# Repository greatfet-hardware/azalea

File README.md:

# Azalea

Hardware licensed under the BSD 3 clause license
Documentation licensed under the BSD 3 clause license

This repository contains the KiCad design for Azalea, also known as GreatFET One.  The design requires:

https://github.com/greatscottgadgets/gsg-kicad-lib

If you are using git, the preferred way to install gsg-kicad-lib is to use the submodule:

```
git submodule init && git submodule update
```

## Overview

Also known as GreatFET One, Azalea is the main board of the GreatFET project.

Azalea is a peripheral interface tool.  By adding expansion boards called "neighbors", you can turn Azalea into a USB peripheral that does almost anything.

Features:
* LPC4330 microcontroller (U1)
* Hi-Speed USB port (USB0) for connection to a host computer
* Expansion interface (J1 and J2) of 80 pins (2 female headers with 2 rows of 20 pins)
* Bonus row of 20 male pins (J7)
* 4 indicator LEDs
* 2 buttons, primarily for development (DFU and RESET, just like HackRF One)
* Full Speed USB port (USB1) for connection to a target (for [Facedancer](https://github.com/usb-tools/Facedancer))
* Power switching for use of USB1 as either host or device
* 3.3 V regulator that can supply some power to neighbors
* 2 MB flash memory
* Unpopulated Cortex Debug Header (J5) for JTAG or SWD

Except where noted below, all pins on expansion ports use 3.3 V I/O voltage.

## J1 (NEIGHBOR1) Pinout

Pin|Symbol|Special Function|Notes    |U1 Pin|GPIO |U0 |U1 |U2  |EMC        |SGPIO|ENET      |CAN1|SSP0|SSP1|I2S0           |I2S1  |USB0     |USB1     |SD   |MISC   |PWM  |TIMER  |SCT     
---|------|----------------|---------|------|-----|---|---|----|-----------|-----|----------|----|----|----|---------------|------|---------|---------|-----|-------|-----|-------|--------
1  |GND   |                |         |      |     |   |   |    |           |     |          |    |    |    |               |      |         |         |     |       |     |       |        
2  |VCC   |                |3.3 V    |      |     |   |   |    |           |     |          |    |    |    |               |      |         |         |     |       |     |       |        
3  |P4_9  |                |         |33    |5[13]|   |   |    |           |14   |          |RD  |    |    |               |      |         |         |     |       |     |       |CTIN_6  
4  |P0_0  |                |         |32    |0[0] |   |   |    |           |0    |RXD1      |    |    |CIPO|TX_WS          |TX_WS |         |         |     |       |     |       |        
5  |P4_10 |                |         |35    |5[14]|   |   |    |           |15   |          |    |    |    |               |      |         |         |     |       |     |       |CTIN_2  
6  |P0_1  |                |         |34    |0[1] |   |   |    |           |1    |TX_EN     |    |    |COPI|               |TX_SDA|         |         |     |       |     |       |        
7  |P1_0  |                |         |38    |0[4] |   |   |    |A5         |7    |          |    |CS  |    |               |      |         |         |     |       |     |       |CTIN_3  
8  |P5_0  |                |         |37    |2[9] |   |DSR|    |D12        |     |          |    |    |    |               |      |         |         |     |       |MCOB2|T1_CAP0|        
9  |P5_1  |                |         |39    |2[10]|   |DTR|    |D13        |     |          |    |    |    |               |      |         |         |     |       |MCI2 |T1_CAP1|        
10 |P1_1  |boot mode       |pull-up  |42    |0[8] |   |   |    |A6         |8    |          |    |CIPO|    |               |      |         |         |     |       |     |       |CTOUT_7 
11 |CLK0  |                |         |45    |     |   |   |    |CLK0, CLK01|     |REF_CLK   |    |    |SCK |               |      |         |         |CLK  |CLKOUT |     |       |        
12 |P1_2  |boot mode       |pull-down|43    |0[9] |   |   |    |A7         |9    |          |    |COPI|    |               |      |         |         |     |       |     |       |CTOUT_6 
13 |P1_5  |                |         |48    |1[8] |   |   |    |CS0#       |15   |          |    |    |CS  |               |      |PWR_FAULT|         |POW  |       |     |       |CTOUT_10
14 |P5_2  |                |         |46    |2[11]|   |RTS|    |D14        |     |          |    |    |    |               |      |         |         |     |       |MCI1 |T1_CAP2|        
15 |P1_7  |                |         |50    |1[0] |   |DSR|    |D0         |     |          |    |    |    |               |      |PPWR     |         |     |       |     |       |CTIN_1  
16 |P1_6  |                |         |49    |1[9] |   |   |    |WE#        |14   |          |    |    |    |               |      |         |         |CMD  |       |     |       |CTIN_5  
17 |P1_9  |                |         |52    |1[2] |   |RTS|    |D2         |     |          |    |    |    |               |      |         |         |DAT0 |       |     |       |CTOUT_11
18 |P1_8  |                |         |51    |1[1] |   |DTR|    |D1         |     |          |    |    |    |               |      |         |         |VOLT0|       |     |       |CTOUT_12
19 |P5_3  |                |         |54    |2[12]|   |RI |    |D15        |     |          |    |    |    |               |      |         |         |     |       |MCI0 |T1_CAP3|        
20 |P1_10 |                |         |53    |1[3] |   |RI |    |D3         |     |          |    |    |    |               |      |         |         |DAT1 |       |     |       |CTOUT_14
21 |P1_12 |                |         |56    |1[5] |   |DCD|    |D5         |8    |          |    |    |    |               |      |         |         |DAT3 |       |     |T0_CAP1|        
22 |P1_11 |                |         |55    |1[4] |   |CTS|    |D4         |     |          |    |    |    |               |      |         |         |DAT2 |       |     |       |CTOUT_15
23 |P5_5  |                |         |58    |2[14]|   |DCD|    |D9         |     |          |    |    |    |               |      |         |         |     |       |MCOA1|T1_MAT1|        
24 |P5_4  |                |         |57    |2[13]|   |CTS|    |D8         |     |          |    |    |    |               |      |         |         |     |       |MCOB0|T1_MAT0|        
25 |P1_14 |                |         |61    |1[7] |   |RXD|    |D7         |10   |          |    |    |    |               |      |         |         |     |       |     |T0_MAT2|        
26 |P1_13 |                |         |60    |1[6] |   |TXD|    |D6         |9    |          |    |    |    |               |      |         |         |CD   |       |     |T0_CAP0|        
27 |P5_6  |                |         |63    |2[15]|   |TXD|    |D10        |     |          |    |    |    |               |      |         |         |     |       |MCOB1|T1_MAT2|        
28 |P1_15 |                |         |62    |0[2] |   |   |TXD |           |2    |RXD0      |    |    |    |               |      |         |         |     |       |     |T0_MAT1|        
29 |P5_7  |                |         |65    |2[7] |   |RXD|    |D11        |     |          |    |    |    |               |      |         |         |     |       |     |T1_MAT3|        
30 |P1_16 |                |         |64    |0[3] |   |   |RXD |           |3    |CRS, RX_DV|    |    |    |               |      |         |         |     |       |MCOA2|T0_MAT0|        
31 |P1_18 |                |         |67    |0[13]|   |   |DIR |           |12   |TXD0      |RD  |    |    |               |      |         |         |     |       |     |T0_MAT3|        
32 |P1_17 |                |         |66    |0[12]|   |   |UCLK|           |11   |MDIO      |TD  |    |    |               |      |         |         |     |       |     |T0_CAP3|        
33 |P9_5  |                |         |69    |5[18]|TXD|   |    |           |3    |          |    |    |    |               |      |         |PPWR     |     |       |MCOA1|       |        
34 |P9_6  |                |         |72    |4[11]|RXD|   |    |           |8    |          |    |    |    |               |      |         |PWR_FAULT|     |       |MCOB1|       |        
35 |P2_0  |                |         |75    |5[0] |TXD|   |    |A13        |4    |MDC       |    |    |    |               |      |PPWR     |         |     |ISP_TXD|     |T3_CAP0|        
36 |P6_0  |                |         |73    |     |   |   |    |           |     |          |    |    |    |RX_MCLK, RX_SCK|      |         |         |     |       |     |       |        
37 |P1_20 |                |         |70    |0[15]|   |   |    |           |13   |TXD1      |    |    |CS  |               |      |         |         |     |       |     |T0_CAP2|        
38 |P1_19 |                |         |68    |     |   |   |    |           |     |REF_CLK   |    |    |SCK |RX_MCLK        |TX_SCK|         |         |     |CLKOUT |     |       |        
39 |P1_4  |                |         |47    |0[11]|   |   |    |BLS0#      |11   |          |    |    |COPI|               |      |IND0     |         |VOLT1|       |     |       |CTOUT_9 
40 |P1_3  |                |         |44    |0[10]|   |   |    |OE#        |10   |          |    |    |CIPO|               |      |IND1     |         |     |       |     |       |CTOUT_8 

## J2 (NEIGHBOR2) Pinout

Pin|Symbol  |Special Function|Notes            |U1 Pin|GPIO |U0  |U1 |U2 |U3  |EMC        |SGPIO|RMII|CAN0|CAN1|SPI |SSP0      |SSP1|SPIFI|I2S0                            |I2S1  |I2C0|I2C1|USB0     |USB1|SD |ADC     |MISC              |PWM  |TIMER  |SCT     
---|--------|----------------|-----------------|------|-----|----|---|---|----|-----------|-----|----|----|----|----|----------|----|-----|--------------------------------|------|----|----|---------|----|---|--------|------------------|-----|-------|--------
1  |GND     |                |                 |      |     |    |   |   |    |           |     |    |    |    |    |          |    |     |                                |      |    |    |         |    |   |        |                  |     |       |        
2  |5V      |                |                 |      |     |    |   |   |    |           |     |    |    |    |    |          |    |     |                                |      |    |    |         |    |   |        |                  |     |       |        
3  |P4_8    |                |                 |15    |5[12]|    |   |   |    |           |13   |    |    |TD  |    |          |    |     |                                |      |    |    |         |    |   |        |                  |     |       |CTIN_5  
4  |P4_0    |                |                 |1     |2[0] |    |   |   |UCLK|           |     |    |    |    |    |          |    |     |                                |      |    |    |         |    |   |        |NMI               |MCOA0|       |        
5  |ADC0_0  |                |                 |6     |     |    |   |   |    |           |     |    |    |    |    |          |    |     |                                |      |    |    |         |    |   |0_0, 1_0|DAC               |     |       |        
6  |P4_5    |                |                 |10    |2[5] |    |   |   |    |           |11   |    |    |    |    |          |    |     |                                |      |    |    |         |    |   |        |                  |     |       |CTOUT_5 
7  |P4_4    |                |                 |9     |2[4] |    |   |   |DIR |           |10   |    |    |    |    |          |    |     |                                |      |    |    |         |    |   |        |DAC               |     |       |CTOUT_2 
8  |P4_2    |                |                 |8     |2[2] |    |   |   |RXD |           |8    |    |    |    |    |          |    |     |                                |      |    |    |         |    |   |        |                  |     |       |CTOUT_0 
9  |P4_3    |                |                 |7     |2[3] |    |   |   |BAUD|           |9    |    |    |    |    |          |    |     |                                |      |    |    |         |    |   |0_0     |                  |     |       |CTOUT_3 
10 |P4_6    |                |                 |11    |2[6] |    |   |   |    |           |12   |    |    |    |    |          |    |     |                                |      |    |    |         |    |   |        |                  |     |       |CTOUT_4 
11 |P4_7    |                |                 |14    |     |    |   |   |    |           |     |    |    |    |    |          |    |     |TX_SCK                          |TX_SCK|    |    |         |    |   |        |GP_CLKIN          |     |       |        
12 |CLK2    |                |                 |99    |     |    |   |   |    |CLK3, CLK23|     |    |    |    |    |          |    |     |TX_MCLK                         |RX_SCK|    |    |         |    |CLK|        |CLKOUT            |     |       |        
13 |P2_8    |DFU, boot mode  |pull-down, button|98    |5[7] |    |   |   |DIR |A8         |15   |    |    |    |    |          |    |     |                                |      |    |    |         |    |   |        |                  |     |       |CTOUT_0 
14 |P2_7    |ISP, boot mode  |pull-up          |96    |0[7] |    |   |   |UCLK|A9         |     |    |    |    |    |          |    |     |                                |      |    |    |         |    |   |        |                  |     |T3_MAT3|CTOUT_1 
15 |P2_6    |                |                 |95    |5[6] |DIR |   |   |    |A10        |7    |    |    |    |    |          |    |     |                                |      |    |    |IND0     |    |   |        |                  |     |T3_CAP3|CTIN_7  
16 |P7_7    |                |                 |140   |3[15]|    |   |   |    |           |7    |MDC |    |    |    |          |    |     |                                |      |    |    |         |    |   |1_6     |TRACEDATA[3]      |     |       |CTOUT_8 
17 |WAKEUP0 |                |pull-up          |130   |     |    |   |   |    |           |     |    |    |    |    |          |    |     |                                |      |    |    |         |    |   |        |WAKEUP0           |     |       |        
18 |P2_5    |                |                 |91    |5[5] |    |   |   |    |           |14   |    |    |    |    |          |    |     |                                |      |    |    |IND0     |VBUS|   |TRIG1   |                  |     |T3_MAT2|CTIN_2  
19 |P2_4    |                |                 |88    |5[4] |    |   |   |RXD |           |13   |    |    |    |    |          |    |     |                                |      |    |SCL |PWR_FAULT|    |   |        |                  |     |T3_MAT1|CTIN_0  
20 |P2_3    |                |                 |87    |5[3] |    |   |   |TXD |           |12   |    |    |    |    |          |    |     |                                |      |    |SDA |PPWR     |    |   |        |                  |     |T3_MAT0|CTIN_1  
21 |PF_4    |                |                 |120   |     |    |   |   |    |           |     |    |    |    |    |          |SCK |     |TX_MCLK, RX_SCK                 |      |    |    |         |    |   |        |GP_CLKIN, TRACECLK|     |       |        
22 |P3_2    |                |                 |116   |5[9] |    |   |   |    |           |     |    |TD  |    |    |          |    |     |TX_SDA, RX_SDA                  |      |    |    |         |IND0|   |        |                  |     |       |        
23 |P7_2    |                |                 |115   |3[10]|    |   |RXD|    |           |6    |    |    |    |    |          |    |     |TX_SDA                          |      |    |    |         |    |   |        |                  |     |       |CTIN_4  
24 |P3_1    |                |                 |114   |5[8] |    |   |   |    |           |     |    |RD  |    |    |          |    |     |TX_WS, RX_WS                    |      |    |    |         |IND1|   |        |                  |     |       |        
25 |P7_1    |                |                 |113   |3[9] |    |   |TXD|    |           |5    |    |    |    |    |          |    |     |TX_WS                           |      |    |    |         |    |   |        |                  |     |       |CTOUT_15
26 |P3_0    |                |                 |112   |     |    |   |   |    |           |     |    |    |    |    |SCK       |    |     |RX_SCK, RX_MCLK, TX_SCK, TX_MCLK|      |    |    |         |    |   |        |                  |     |       |        
27 |P7_0    |                |                 |110   |3[8] |    |   |   |    |           |4    |    |    |    |    |          |    |     |                                |      |    |    |         |    |   |        |                  |     |       |CTOUT_14
28 |P3_4    |                |                 |119   |1[14]|    |TXD|   |    |           |     |    |    |    |    |          |    |SIO3 |TX_WS                           |RX_SDA|    |    |         |    |   |        |                  |     |       |        
29 |P6_8    |                |                 |86    |5[16]|    |   |   |    |A14        |7    |    |    |    |    |          |    |     |                                |      |    |    |IND0     |    |   |        |                  |     |T2_MAT1|        
30 |P3_7    |                |                 |123   |5[10]|    |   |   |    |           |     |    |    |    |COPI|CIPO, COPI|    |COPI |                                |      |    |    |         |    |   |        |                  |     |       |        
31 |P6_7    |                |                 |85    |5[15]|    |   |   |    |A15        |6    |    |    |    |    |          |    |     |                                |      |    |    |IND1     |    |   |        |                  |     |T2_MAT0|        
32 |P3_3    |                |                 |118   |     |    |   |   |    |           |     |    |    |    |SCK |SCK       |    |SCK  |TX_MCLK                         |TX_SCK|    |    |         |    |   |        |CGU_OUT1          |     |       |        
33 |P2_2    |                |                 |84    |5[2] |UCLK|   |   |    |A11        |6    |    |    |    |    |          |    |     |                                |      |    |    |IND1     |    |   |        |                  |     |T3_CAP2|CTIN_6  
34 |P6_6    |                |                 |83    |0[5] |    |   |   |    |BLS1#      |5    |    |    |    |    |          |    |     |                                |      |    |    |PWR_FAULT|    |   |        |                  |     |T2_CAP3|        
35 |P2_1    | neighbor WC    |                 |81    |5[1] |RXD |   |   |    |A12        |5    |    |    |    |    |          |    |     |                                |      |    |    |PWR_FAULT|    |   |        |ISP_RXD           |     |T3_CAP1|        
36 |P6_3    |                |                 |79    |3[2] |    |   |   |    |CS1#       |4    |    |    |    |    |          |    |     |                                |      |    |    |PPWR     |    |   |        |                  |     |T2_CAP2|        
37 |P3_5    |                |                 |121   |1[15]|    |RXD|   |    |           |     |    |    |    |    |          |    |SIO2 |TX_SDA                          |RX_WS |    |    |         |    |   |        |                  |     |       |        
38 |P3_6    |                |                 |122   |0[6] |    |   |   |    |           |     |    |    |    |CIPO|CS,   CIPO|    |CIPO |                                |      |    |    |         |    |   |        |                  |     |       |        
39 |I2C0_SDA|                |pull-up          |93    |     |    |   |   |    |           |     |    |    |    |    |          |    |     |                                |      |SDA |    |         |    |   |        |                  |     |       |        
40 |I2C0_SCL|                |pull-up          |92    |     |    |   |   |    |           |     |    |    |    |    |          |    |     |                                |      |SCL |    |         |    |   |        |                  |     |       |        

## J5 (JTAG) Pinout

Pin|Symbol    |Notes          |U1 Pin
---|----------|---------------|------
1  |VCC       |3.3 V          |      
2  |TMS/SWDIO |               |30    
3  |GND       |               |      
4  |TCK/SWDCLK|pull-up        |27    
5  |GND       |               |      
6  |TDO/SWO   |pull-up        |31    
7  |          |not connected  |      
8  |TDI       |               |26    
9  |GND       |               |      
10 |RESET#    |pull-up, button|128   

## J7 (BONUS_ROW) Pinout

Pin|Symbol       |Special Function|Notes          |U1 Pin|GPIO |U0  |U2  |U3  |EMC    |I2S0  |ADC     |PWM    |TIMER  |SCT    
---|-------------|----------------|---------------|------|-----|----|----|----|-------|------|--------|-------|-------|-------
1  |GND          |                |               |      |     |    |    |    |       |      |        |       |       |       
2  |P6_4         |                |               |80    |3[3] |TXD |    |    |CAS#   |      |        |       |       |CTIN_6 
3  |P6_5         |                |               |82    |3[4] |RXD |    |    |RAS#   |      |        |       |       |CTOUT_6
4  |ADC0_5/ADC1_5|                |               |144   |     |    |    |    |       |      |0_5, 1_5|       |       |       
5  |ADC0_2/ADC1_2|                |               |143   |     |    |    |    |       |      |0_2, 1_2|       |       |       
6  |P2_9         |boot mode       |pull-down      |102   |1[10]|    |    |BAUD|A0     |      |        |       |       |CTOUT_3
7  |P2_12        |                |               |106   |1[12]|    |UCLK|    |A3     |      |        |       |       |CTOUT_4
8  |P2_13        |                |               |108   |1[13]|    |DIR |    |A4     |      |        |       |       |CTIN_4 
9  |RTC_ALARM    |                |               |129   |     |    |    |    |       |      |        |       |       |       
10 |RTCX1        |                |               |      |     |    |    |    |       |      |        |       |       |       
11 |RESET#       |                |pull-up, button|128   |     |    |    |    |       |      |        |       |       |       
12 |VBAT         |                |               |127   |     |    |    |    |       |      |        |       |       |       
13 |P2_11        |                |               |105   |1[11]|    |RXD |    |A2     |      |        |       |       |CTOUT_5
14 |P2_10        |                |               |104   |0[14]|    |TXD |    |A1     |      |        |       |       |CTOUT_2
15 |P6_10        |                |               |100   |3[6] |    |    |    |DQMOUT1|      |        |MCABORT|       |       
16 |P6_9         |                |               |97    |3[5] |    |    |    |DYCS0# |      |        |       |T2_MAT2|       
17 |P6_2         |                |               |78    |3[1] |DIR |    |    |CKEOUT1|RX_SDA|        |       |T2_CAP1|       
18 |P6_1         |                |               |74    |3[0] |UCLK|    |    |DYCS1# |RX_WS |        |       |T2_CAP0|       
19 |GND          |                |               |      |     |    |    |    |       |      |        |       |       |       
20 |VCC          |                |3.3 V          |      |     |    |    |    |       |      |        |       |       |       

## Clear Acrylic Case

Hardware licensed under the BSD 3 clause license
Documentation licensed under the BSD 3 clause license

The vector graphic file provided in this repo was created with Inkscape.

The black lines are the edge cuts. The blue lines are cut outs. The red lines are optional and should be lightly etched if they are used.
The red lines are meant to be used to help count holes in the headers.

### The BOM 

* 4 x 4.5 mm OD Hex Standoffs (Female-Female) / M3-0.5 x 6 mm / Aluminum
* 4 x 4.5 mm OD Hex Standoffs (Female-Female) / M3-0.5 x 5 mm / Aluminum
* 4 x M3-0.5 x 12 mm / Phillips Pan Head Machine Screw
* 4 x M3-0.5 x 5 mm / Phillips Pan Head Machine Screw

Optional:
* 4 (per neighbor) x 4.5 mm OD Hex Standoffs (Male-Female) / M3-0.5 x 11 mm / Aluminum

These standoffs are to be used if a neighbor is stacked on your GreatFET One and you want your case to be stacked above that neighbor.

### Assembly Instructions 

Assembly instructions can be found [here.](https://www.greatscottgadgets.com/greatfet/acrylic-case/)

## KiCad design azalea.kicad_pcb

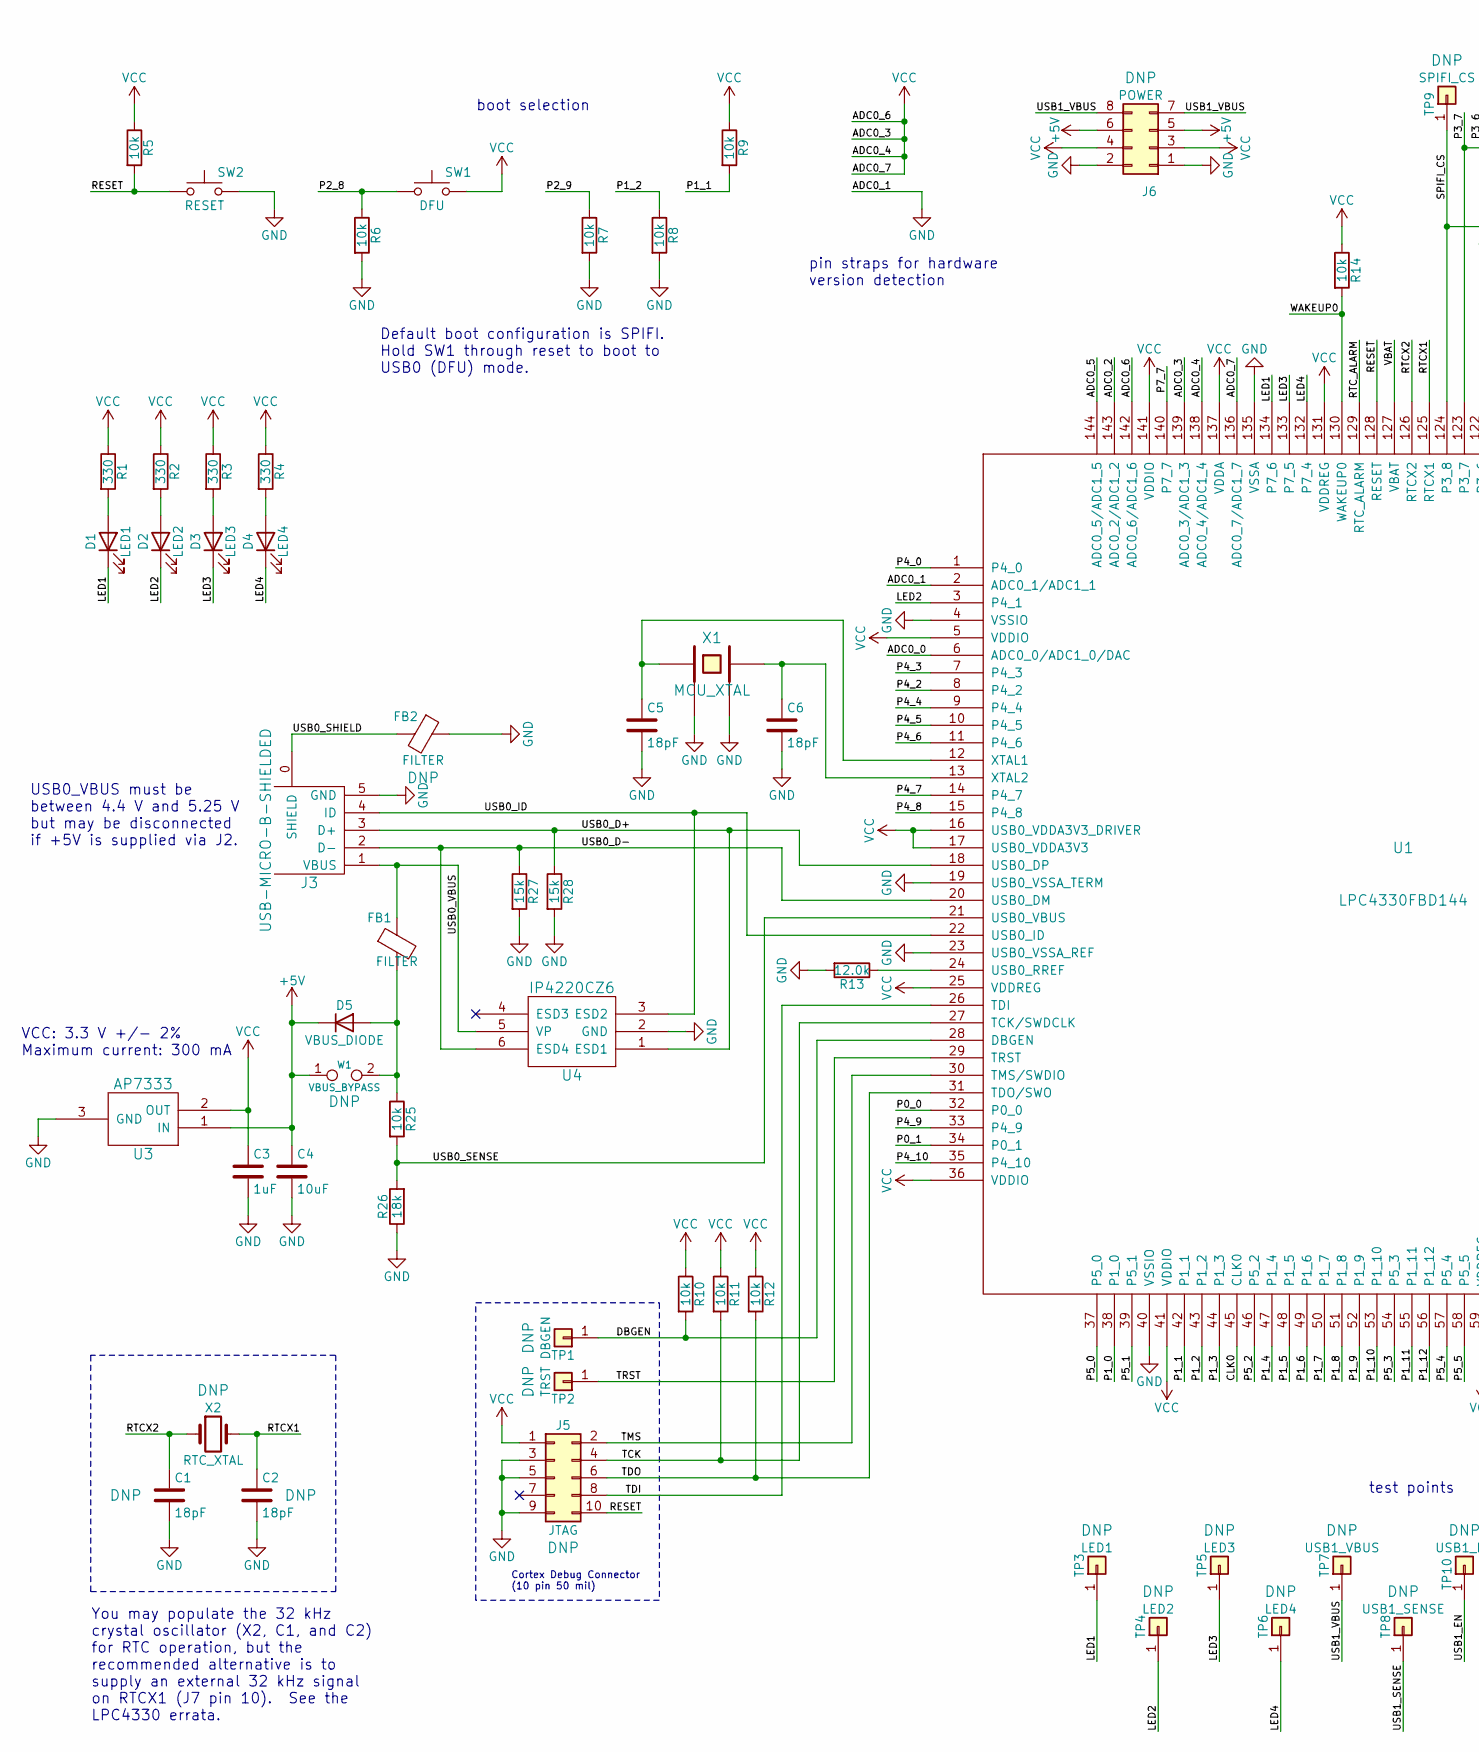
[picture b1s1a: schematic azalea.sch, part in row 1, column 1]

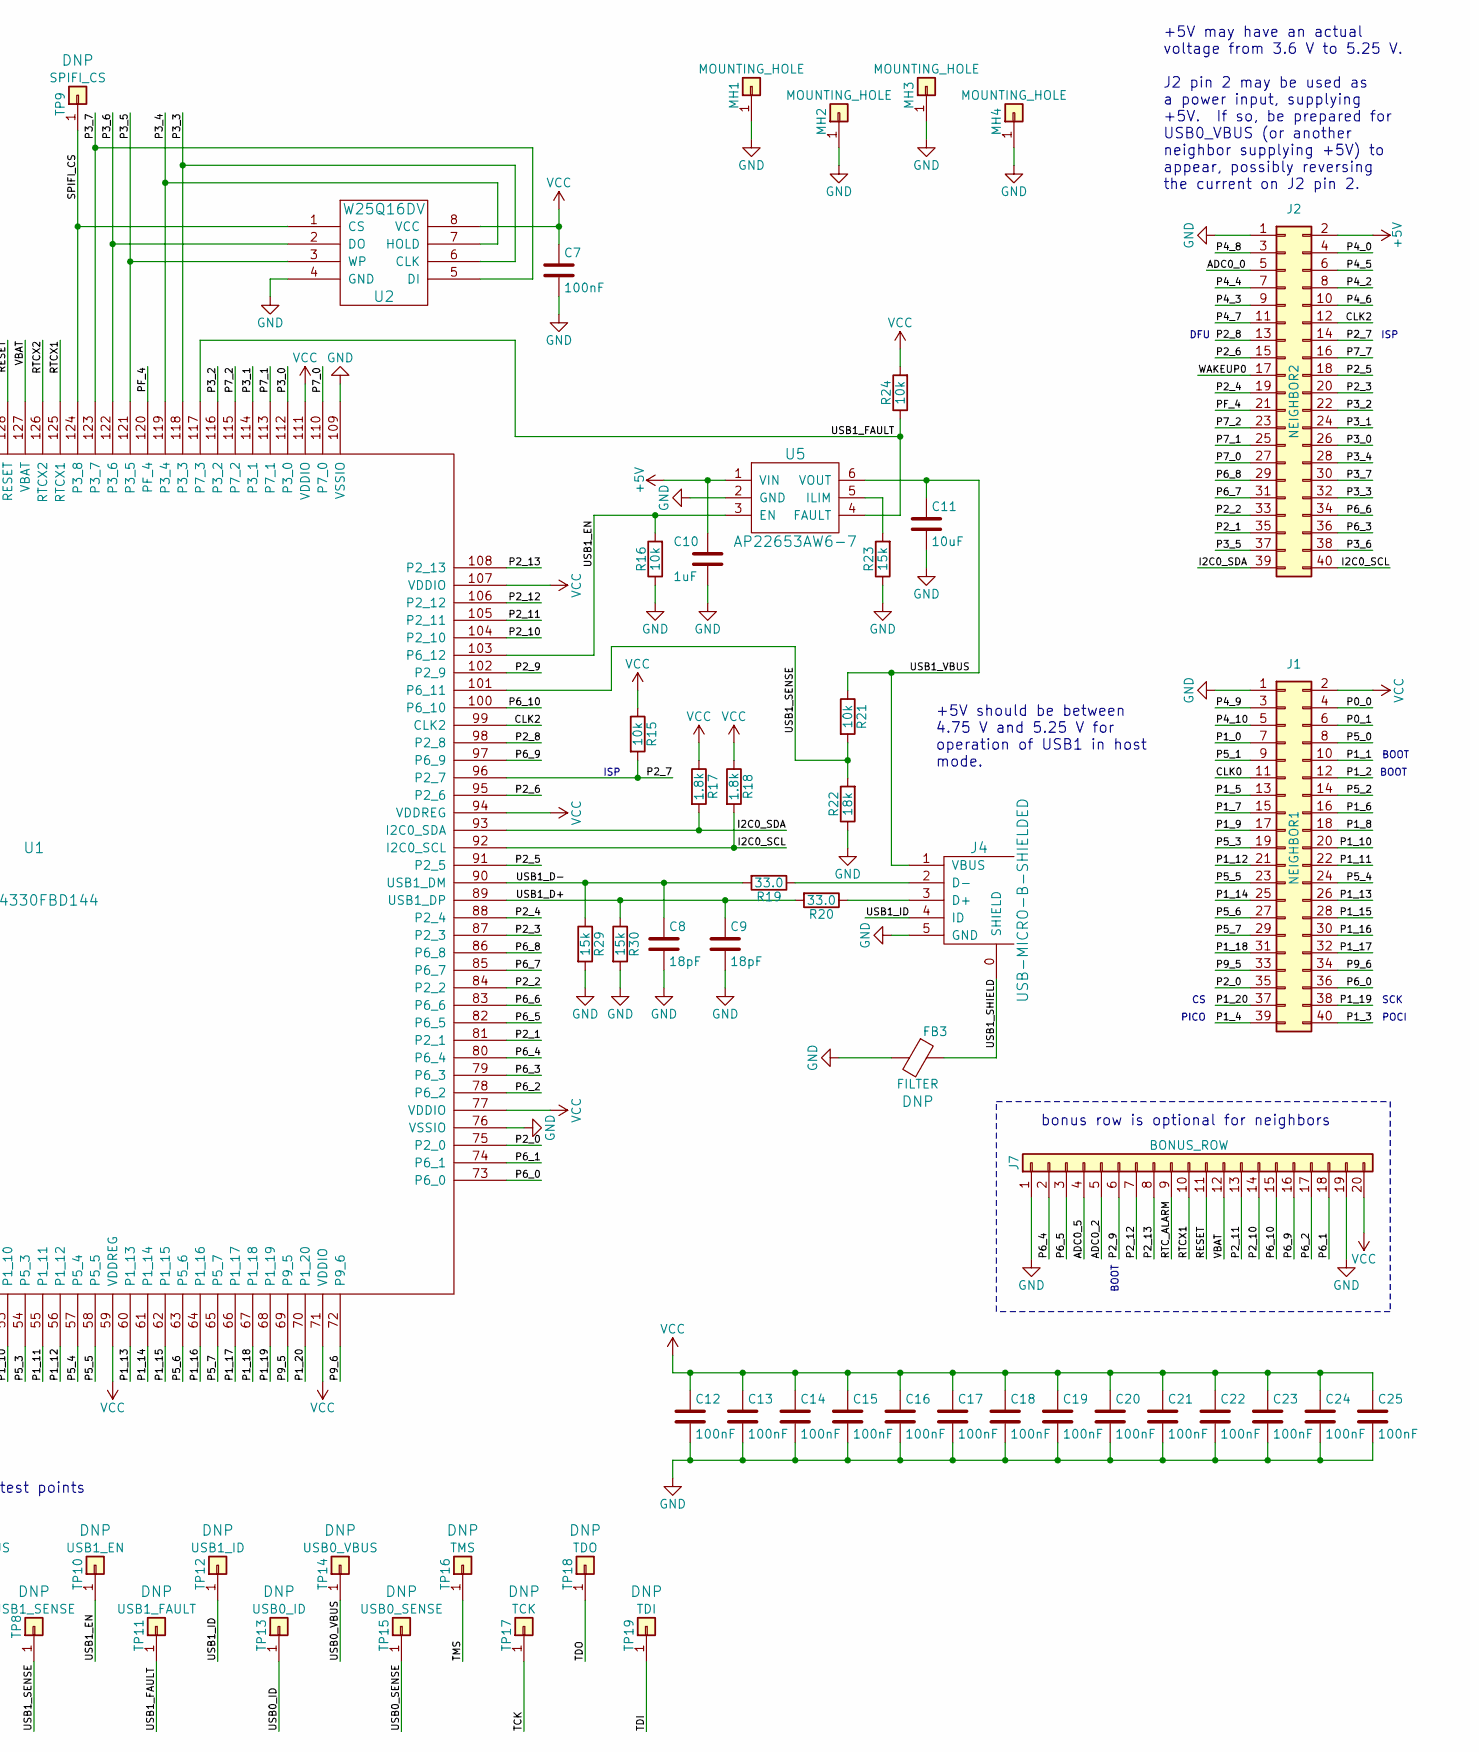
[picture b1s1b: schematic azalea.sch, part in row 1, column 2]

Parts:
C1, C2, C5, C6, C8, C9: 18pF; 0603; Part Number C0603C180J5GAC
C3, C10: 1uF; 0603; Part Number LMK107B7105KA-T
C4, C11: 10uF; 0805; Part Number LMK212ABJ106KG-T
C7, C12, C13, C14, C15, C16, C17, C18, C19, C20, C21, C22, C23, C24, C25: 100nF; 0603; Part Number C0603C104M4RAC
D1: LED1; 0603D; Part Number SML-LX0603GW-TR
D2: LED2; 0603D; Part Number SML-LX0603YW-TR
D3: LED3; 0603D; Part Number SML-LX0603GW-TR
D4: LED4; 0603D; Part Number SML-LX0603YW-TR
D5: VBUS_DIODE; SOD128; Part Number PMEG3050EP,115
FB1, FB2, FB3: FILTER; 0805; Part Number BLM21PG221SN1D
J1: NEIGHBOR1; HEADER-2x20; Part Number SSW-120-01-F-D
J2: NEIGHBOR2; HEADER-2x20; Part Number SSW-120-01-F-D
J3, J4: USB-MICRO-B-SHIELDED; USB-MICROB-FCI-10103592-LONGPADS; Part Number 10103592-0001LF
J5: JTAG; 50MIL-HEADER-2x5-TH
J6: POWER; HEADER-SMT-2x4
J7: BONUS_ROW; HEADER-1x20; Part Number PRPC020SAAN-RC
MH1, MH2, MH3, MH4: MOUNTING_HOLE; HOLE126MIL-COPPER
R1, R2, R3, R4: 330; 0603; Part Number RMCF0603JT330R
R5, R6, R7, R8, R9, R10, R11, R12, R14, R15, R16, R21, R24, R25: 10k; 0603; Part Number ERJ-3GEYJ103V
R13: 12.0k; 0603; Part Number RMCF0603FT12K0
R17, R18: 1.8k; 0603; Part Number RMCF0603JT1K80
R19, R20: 33.0; 0603; Part Number RC0603FR-0733RL
R22, R26: 18k; 0603; Part Number RC0603JR-0718KL
R23, R27, R28, R29, R30: 15k; 0603; Part Number RC0603JR-0715KL
SW1: DFU; SWITCH-PTS840-P; Part Number PTS840 PM SMTR LFS
SW2: RESET; SWITCH-PTS840-P; Part Number PTS840 PM SMTR LFS
TP1: DBGEN; TESTPOINT-50MIL
TP2: TRST; TESTPOINT-50MIL
TP3: LED1; TESTPOINT-50MIL
TP4: LED2; TESTPOINT-50MIL
TP5: LED3; TESTPOINT-50MIL
TP6: LED4; TESTPOINT-50MIL
TP7: USB1_VBUS; TESTPOINT-50MIL
TP8: USB1_SENSE; TESTPOINT-50MIL
TP9: SPIFI_CS; TESTPOINT-50MIL
TP10: USB1_EN; TESTPOINT-50MIL
TP11: USB1_FAULT; TESTPOINT-50MIL
TP12: USB1_ID; TESTPOINT-50MIL
TP13: USB0_ID; TESTPOINT-50MIL
TP14: USB0_VBUS; TESTPOINT-50MIL
TP15: USB0_SENSE; TESTPOINT-50MIL
TP16: TMS; TESTPOINT-50MIL
TP17: TCK; TESTPOINT-50MIL
TP18: TDO; TESTPOINT-50MIL
TP19: TDI; TESTPOINT-50MIL
U1: LPC4330FBD144; LQFP144; Part Number LPC4330FBD144,551
U2: W25Q16DV; SOIC8-208; Part Number W25Q16JVSSIQ
U3: AP7333; SOT23-3; Part Number AP7333-33SAG-7
U4: IP4220CZ6; SOT457; Part Number IP4220CZ6,125
U5: AP22653AW6-7; SOT457; Part Number AP22653AW6-7
W1: VBUS_BYPASS; 0603-JUMPER
X1: MCU_XTAL; XTAL3.2x2.5mm-EXT; Part Number 7V-12.000MAAE-T
X2: RTC_XTAL; XTAL-AB26TRQ; Part Number AB26TRQ-32.768KHZ-T

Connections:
+5V: C4.1, C10.1, D5.1 (K), J2.2, J6.5, J6.6, U3.1 (IN), U5.1 (VIN), W1.1
/ADC0_0: J2.5, U1.6 (ADC0_0/ADC1_0/DAC)
/ADC0_2: J7.5, U1.143 (ADC0_2/ADC1_2)
/ADC0_5: J7.4, U1.144 (ADC0_5/ADC1_5)
/CLK0: J1.11, U1.45 (CLK0)
/CLK2: J2.12, U1.99 (CLK2)
/DBGEN: R10.2, TP1.1, U1.28 (DBGEN)
/I2C0_SCL: J2.40, R18.2, U1.92 (I2C0_SCL)
/I2C0_SDA: J2.39, R17.2, U1.93 (I2C0_SDA)
/LED1: D1.1 (K), TP3.1, U1.134 (P7_6)
/LED2: D2.1 (K), TP4.1, U1.3 (P4_1)
/LED3: D3.1 (K), TP5.1, U1.133 (P7_5)
/LED4: D4.1 (K), TP6.1, U1.132 (P7_4)
/P0_0: J1.4, U1.32 (P0_0)
/P0_1: J1.6, U1.34 (P0_1)
/P1_0: J1.7, U1.38 (P1_0)
/P1_1: J1.10, R9.2, U1.42 (P1_1)
/P1_2: J1.12, R8.1, U1.43 (P1_2)
/P1_3: J1.40, U1.44 (P1_3)
/P1_4: J1.39, U1.47 (P1_4)
/P1_5: J1.13, U1.48 (P1_5)
/P1_6: J1.16, U1.49 (P1_6)
/P1_7: J1.15, U1.50 (P1_7)
/P1_8: J1.18, U1.51 (P1_8)
/P1_9: J1.17, U1.52 (P1_9)
/P1_10: J1.20, U1.53 (P1_10)
/P1_11: J1.22, U1.55 (P1_11)
/P1_12: J1.21, U1.56 (P1_12)
/P1_13: J1.26, U1.60 (P1_13)
/P1_14: J1.25, U1.61 (P1_14)
/P1_15: J1.28, U1.62 (P1_15)
/P1_16: J1.30, U1.64 (P1_16)
/P1_17: J1.32, U1.66 (P1_17)
/P1_18: J1.31, U1.67 (P1_18)
/P1_19: J1.38, U1.68 (P1_19)
/P1_20: J1.37, U1.70 (P1_20)
/P2_0: J1.35, U1.75 (P2_0)
/P2_1: J2.35, U1.81 (P2_1)
/P2_2: J2.33, U1.84 (P2_2)
/P2_3: J2.20, U1.87 (P2_3)
/P2_4: J2.19, U1.88 (P2_4)
/P2_5: J2.18, U1.91 (P2_5)
/P2_6: J2.15, U1.95 (P2_6)
/P2_7: J2.14, R15.2, U1.96 (P2_7)
/P2_8: J2.13, R6.1, SW1.1, U1.98 (P2_8)
/P2_9: J7.6, R7.1, U1.102 (P2_9)
/P2_10: J7.14, U1.104 (P2_10)
/P2_11: J7.13, U1.105 (P2_11)
/P2_12: J7.7, U1.106 (P2_12)
/P2_13: J7.8, U1.108 (P2_13)
/P3_0: J2.26, U1.112 (P3_0)
/P3_1: J2.24, U1.114 (P3_1)
/P3_2: J2.22, U1.116 (P3_2)
/P3_3: J2.32, U1.118 (P3_3), U2.6 (CLK)
/P3_4: J2.28, U1.119 (P3_4), U2.7 (HOLD)
/P3_5: J2.37, U1.121 (P3_5), U2.3 (WP)
/P3_6: J2.38, U1.122 (P3_6), U2.2 (DO)
/P3_7: J2.30, U1.123 (P3_7), U2.5 (DI)
/P4_0: J2.4, U1.1 (P4_0)
/P4_2: J2.8, U1.8 (P4_2)
/P4_3: J2.9, U1.7 (P4_3)
/P4_4: J2.7, U1.9 (P4_4)
/P4_5: J2.6, U1.10 (P4_5)
/P4_6: J2.10, U1.11 (P4_6)
/P4_7: J2.11, U1.14 (P4_7)
/P4_8: J2.3, U1.15 (P4_8)
/P4_9: J1.3, U1.33 (P4_9)
/P4_10: J1.5, U1.35 (P4_10)
/P5_0: J1.8, U1.37 (P5_0)
/P5_1: J1.9, U1.39 (P5_1)
/P5_2: J1.14, U1.46 (P5_2)
/P5_3: J1.19, U1.54 (P5_3)
/P5_4: J1.24, U1.57 (P5_4)
/P5_5: J1.23, U1.58 (P5_5)
/P5_6: J1.27, U1.63 (P5_6)
/P5_7: J1.29, U1.65 (P5_7)
/P6_0: J1.36, U1.73 (P6_0)
/P6_1: J7.18, U1.74 (P6_1)
/P6_2: J7.17, U1.78 (P6_2)
/P6_3: J2.36, U1.79 (P6_3)
/P6_4: J7.2, U1.80 (P6_4)
/P6_5: J7.3, U1.82 (P6_5)
/P6_6: J2.34, U1.83 (P6_6)
/P6_7: J2.31, U1.85 (P6_7)
/P6_8: J2.29, U1.86 (P6_8)
/P6_9: J7.16, U1.97 (P6_9)
/P6_10: J7.15, U1.100 (P6_10)
/P7_0: J2.27, U1.110 (P7_0)
/P7_1: J2.25, U1.113 (P7_1)
/P7_2: J2.23, U1.115 (P7_2)
/P7_7: J2.16, U1.140 (P7_7)
/P9_5: J1.33, U1.69 (P9_5)
/P9_6: J1.34, U1.72 (P9_6)
/PF_4: J2.21, U1.120 (PF_4)
/RESET: J5.10, J7.11, R5.2, SW2.1, U1.128 (RESET)
/RTCX1: C2.1, J7.10, U1.125 (RTCX1), X2.2
/RTCX2: C1.1, U1.126 (RTCX2), X2.1
/RTC_ALARM: J7.9, U1.129 (RTC_ALARM)
/SPIFI_CS: TP9.1, U1.124 (P3_8), U2.1 (CS)
/TCK: J5.4, R11.2, TP17.1, U1.27 (TCK/SWDCLK)
/TDI: J5.8, TP19.1, U1.26 (TDI)
/TDO: J5.6, R12.2, TP18.1, U1.31 (TDO/SWO)
/TMS: J5.2, TP16.1, U1.30 (TMS/SWDIO)
/TRST: TP2.1, U1.29 (TRST)
/USB0_D+: J3.3 (D+), R28.1, U1.18 (USB0_DP), U4.1 (ESD1)
/USB0_D-: J3.2 (D-), R27.1, U1.20 (USB0_DM), U4.6 (ESD4)
/USB0_ID: J3.4 (ID), TP13.1, U1.22 (USB0_ID), U4.3 (ESD2)
/USB0_SENSE: R25.2, R26.2, TP15.1, U1.21 (USB0_VBUS)
/USB0_SHIELD: FB2.2, J3.0 (SHIELD)
/USB0_VBUS: FB1.1, J3.1 (VBUS), TP14.1, U4.5 (VP)
/USB1_D+: C9.1, R20.2, R30.1, U1.89 (USB1_DP)
/USB1_D-: C8.1, R19.2, R29.1, U1.90 (USB1_DM)
/USB1_EN: R16.2, TP10.1, U1.103 (P6_12), U5.3 (EN)
/USB1_FAULT: R24.1, TP11.1, U1.117 (P7_3), U5.4 (FAULT)
/USB1_ID: J4.4 (ID), TP12.1
/USB1_SENSE: R21.2, R22.2, TP8.1, U1.101 (P6_11)
/USB1_SHIELD: FB3.1, J4.0 (SHIELD)
/USB1_VBUS: C11.1, J4.1 (VBUS), J6.7, J6.8, R21.1, TP7.1, U5.6 (VOUT)
/VBAT: J7.12, U1.127 (VBAT)
/WAKEUP0: J2.17, R14.2, U1.130 (WAKEUP0)
GND: C1.2, C2.2, C3.2, C4.2, C5.2, C6.2, C7.2, C8.2, C9.2, C10.2, C11.2, C12.2, C13.2, C14.2, C15.2, C16.2, C17.2, C18.2, C19.2, C20.2, C21.2, C22.2, C23.2, C24.2, C25.2, FB2.1, FB3.2, J1.1, J2.1, J3.5 (GND), J4.5 (GND), J5.3, J5.5, J5.9, J6.1, J6.2, J7.1, J7.19, MH1.1, MH2.1, MH3.1, MH4.1, R6.2, R7.2, R8.2, R13.2, R16.1, R22.1, R23.1, R26.1, R27.2, R28.2, R29.2, R30.2, SW2.2, U1.2 (ADC0_1/ADC1_1), U1.4 (VSSIO), U1.19 (USB0_VSSA_TERM), U1.23 (USB0_VSSA_REF), U1.40 (VSSIO), U1.76 (VSSIO), U1.109 (VSSIO), U1.135 (VSSA), U2.4 (GND), U3.3 (GND), U4.2 (GND), U5.2 (GND), X1.2, X1.4
unnamed: C5.1, U1.12 (XTAL1), X1.1
unnamed: C6.1, U1.13 (XTAL2), X1.3
unnamed: D1.2 (A), R1.2
unnamed: D2.2 (A), R2.2
unnamed: D3.2 (A), R3.2
unnamed: D4.2 (A), R4.2
unnamed: D5.2 (A), FB1.2, R25.1, W1.2
unnamed: J4.2 (D-), R19.1
unnamed: J4.3 (D+), R20.1
unnamed: R13.1, U1.24 (USB0_RREF)
unnamed: R23.2, U5.5 (ILIM)
VCC: C3.1, C7.1, C12.1, C13.1, C14.1, C15.1, C16.1, C17.1, C18.1, C19.1, C20.1, C21.1, C22.1, C23.1, C24.1, C25.1, J1.2, J5.1, J6.3, J6.4, J7.20, R1.1, R2.1, R3.1, R4.1, R5.1, R9.1, R10.1, R11.1, R12.1, R14.1, R15.1, R17.1, R18.1, R24.2, SW1.2, U1.5 (VDDIO), U1.16 (USB0_VDDA3V3_DRIVER), U1.17 (USB0_VDDA3V3), U1.25 (VDDREG), U1.36 (VDDIO), U1.41 (VDDIO), U1.59 (VDDREG), U1.71 (VDDIO), U1.77 (VDDIO), U1.94 (VDDREG), U1.107 (VDDIO), U1.111 (VDDIO), U1.131 (VDDREG), U1.136 (ADC0_7/ADC1_7), U1.137 (VDDA), U1.138 (ADC0_4/ADC1_4), U1.139 (ADC0_3/ADC1_3), U1.141 (VDDIO), U1.142 (ADC0_6/ADC1_6), U2.8 (VCC), U3.2 (OUT)

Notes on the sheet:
POCI
PICO
SCK
ISP
DFU
BOOT
bonus row is optional for neighbors
boot selection
test points
Default boot configuration is SPIFI. Hold SW1 through reset to boot to USB0 (DFU) mode.
Cortex Debug Connector (10 pin 50 mil)
VCC: 3.3 V +/- 2% Maximum current: 300 mA
USB0_VBUS must be between 4.4 V and 5.25 V but may be disconnected if +5V is supplied via J2.
+5V may have an actual voltage from 3.6 V to 5.25 V. J2 pin 2 may be used as a power input, supplying +5V. If so, be prepared for USB0_VBUS (or another neighbor supplying +5V) to appear, possibly reversing the current on J2 pin 2.
+5V should be between 4.75 V and 5.25 V for operation of USB1 in host mode.
pin straps for hardware version detection
You may populate the 32 kHz crystal oscillator (X2, C1, and C2) for RTC operation, but the recommended alternative is to supply an external 32 kHz signal on RTCX1 (J7 pin 10). See the LPC4330 errata.

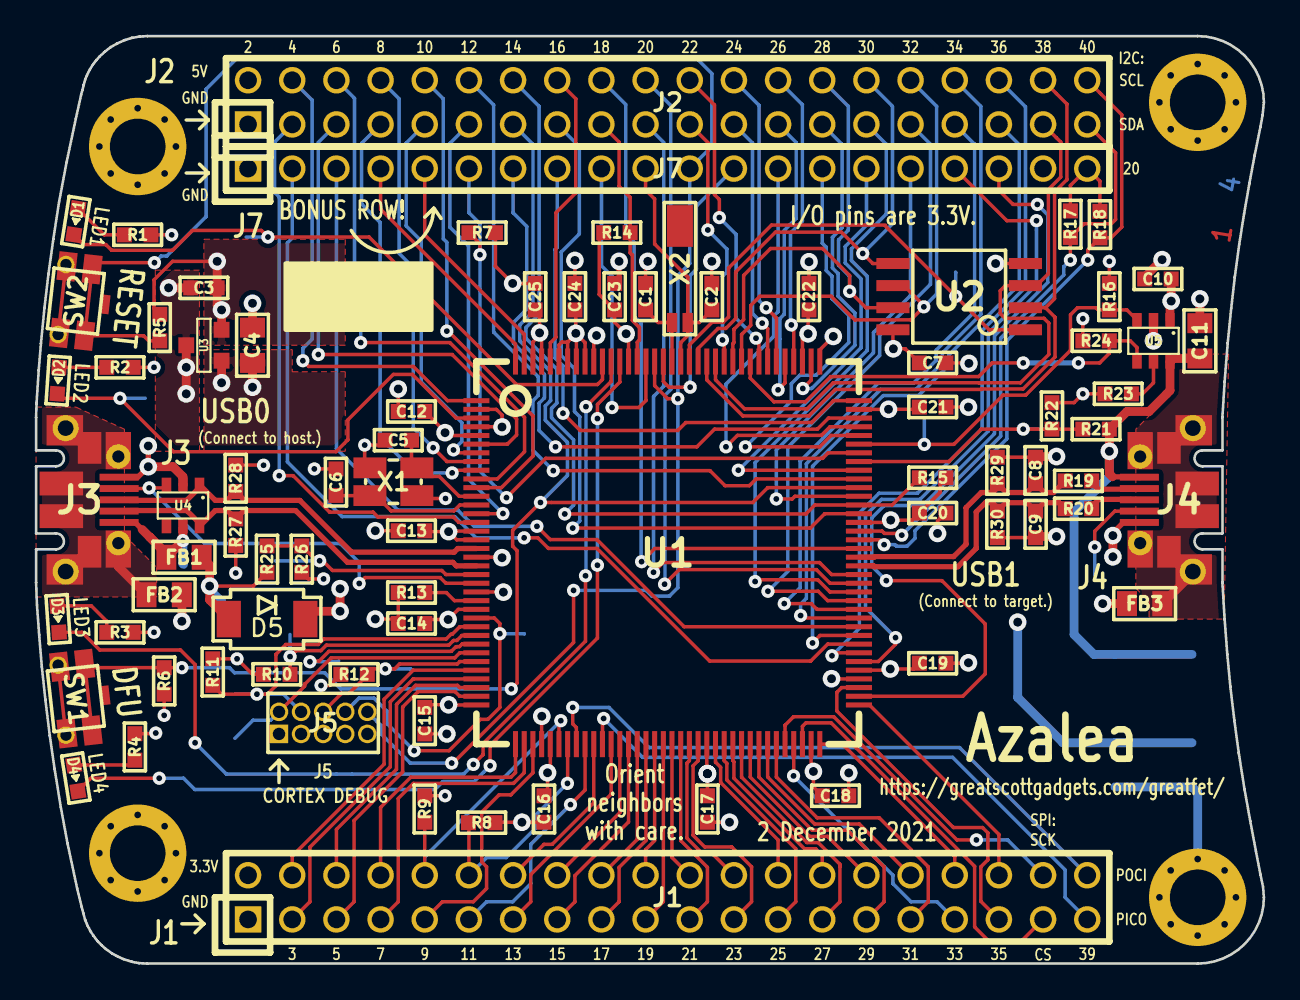
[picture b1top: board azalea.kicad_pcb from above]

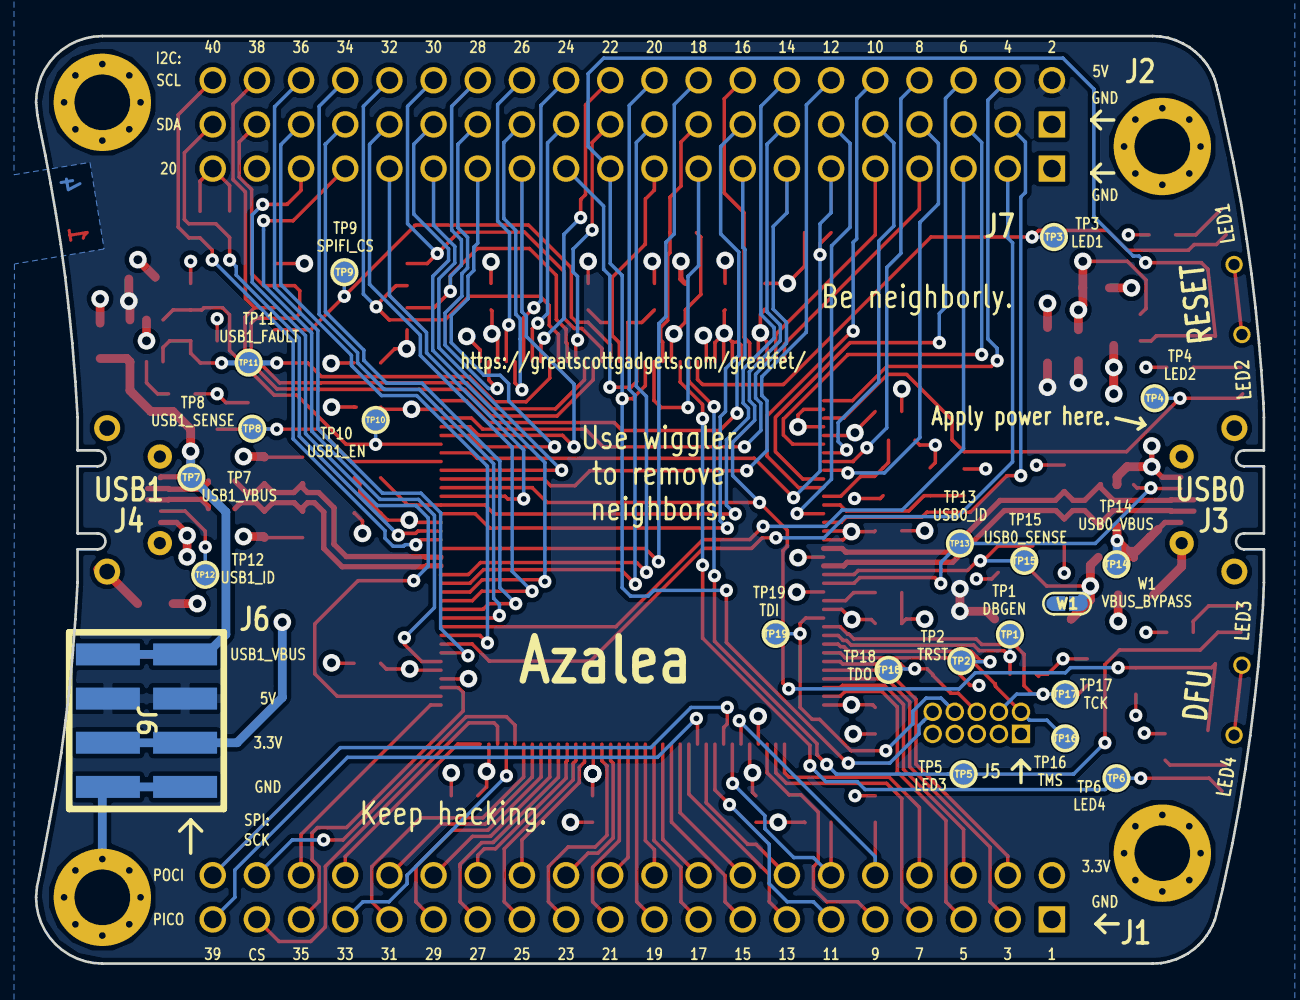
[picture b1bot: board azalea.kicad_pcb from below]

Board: 4 copper layers, 70.6 x 53.3 mm, 103 parts (21 on the bottom side), 133 nets.

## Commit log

2019-05-27 split azalea into separate repository
2019-05-27 updated README.md to be azalea-specific
2019-08-30 Added acrylic case svg file; updated README to include acrylic case
2019-08-30 Fixed link to svg file.
2019-09-10 Removed link to AC.GF1 in the README
2019-09-10 Spell check
2019-10-09 Added licensing info to the README file in two places - under Azalea header, and under Acrylic Case header
2020-07-03 adopt OSHWA convention for SPI signal names https://www.oshwa.org/a-resolution-to-redefine-spi-signal-names
2020-07-03 correct additional signal names in README
2021-11-24 GF1 Hardware: Update schematic for modern KiCAD
2021-11-24 GF1 Hardware: Rotate FB symbols to correct orientation.
2021-11-29 GF1 hardware: Update U5 & R23 with AP22653AW6-7 p/n and res value.
2021-11-29 GF1 hardware: Update PCB to reflect U5 & R23 peart changes.
2021-12-03 GF1 hardware: Update references from MOSI/MISO or COPI/CIPO to PICO/POCI
2022-03-08 update date on silkscreen

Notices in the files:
azalea.kicad_pcb:
Copyright 2015-2021 Great Scott Gadgets
License: BSD-3-Clause
